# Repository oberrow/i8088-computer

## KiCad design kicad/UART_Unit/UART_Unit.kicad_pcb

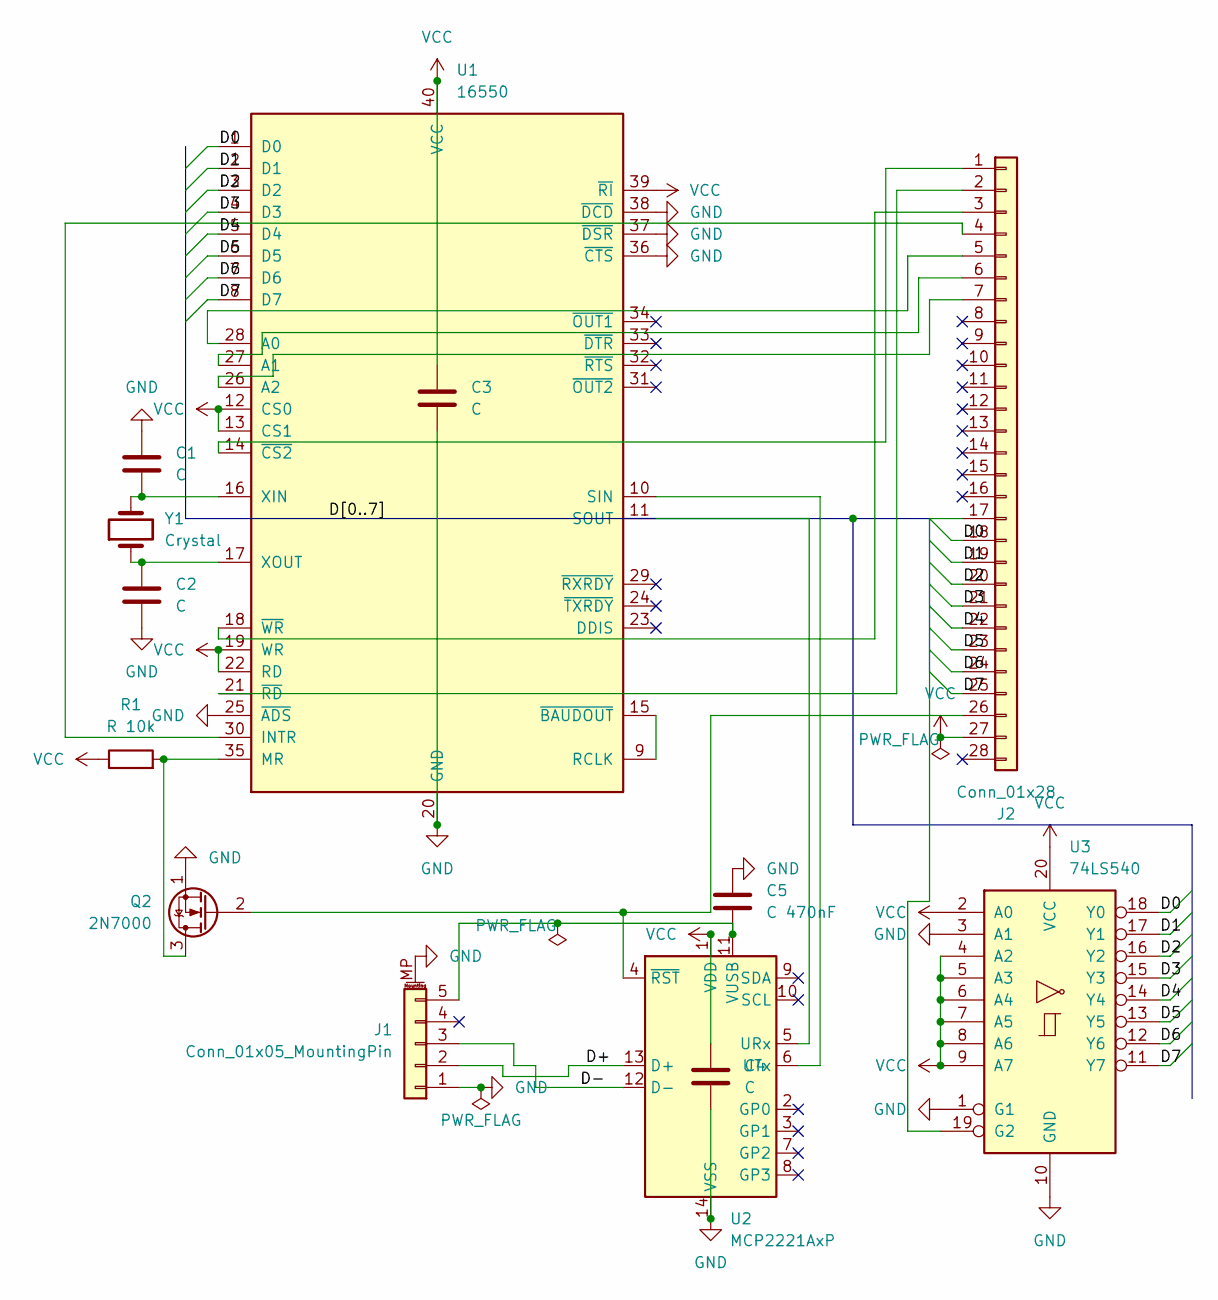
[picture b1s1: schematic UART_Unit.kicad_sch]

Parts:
C1, C2: C; C_Disc_D5.0mm_W2.5mm_P5.00mm
C3, C4: C; C_Disc_D5.0mm_W2.5mm_P2.50mm
C5: C 470nF; C_Disc_D5.0mm_W2.5mm_P2.50mm
J1: Conn_01x05_MountingPin; Molex_200528-0050_1x05-1MP_P1.00mm_Horizontal
J2: Conn_01x28; PinHeader_2x14_P2.54mm_Vertical
Q2: 2N7000; TO-92_Inline
R1: R 10k; R_Axial_DIN0207_L6.3mm_D2.5mm_P10.16mm_Horizontal
U1: 16550; DIP-40_W15.24mm
U2: MCP2221AxP; DIP-14_W7.62mm
U3: 74LS540; DIP-20_W7.62mm
Y1: Crystal; Crystal_HC49-U_Vertical

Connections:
/D0: J2.18, U1.1 (D0), U3.18 (Y0)
/D1: J2.19, U1.2 (D1), U3.17 (Y1)
/D2: J2.20, U1.3 (D2), U3.16 (Y2)
/D3: J2.21, U1.4 (D3), U3.15 (Y3)
/D4: J2.22, U1.5 (D4), U3.14 (Y4)
/D5: J2.23, U1.6 (D5), U3.13 (Y5)
/D6: J2.24, U1.7 (D6), U3.12 (Y6)
/D7: J2.25, U1.8 (D7), U3.11 (Y7)
/D+: J1.2, U2.13 (D+)
/D-: J1.3, U2.12 (D-)
GND: C1.1, C2.2, C3.2, C4.2, C5.1, J1.1, J1.MP (MountPin), Q2.1 (S), U1.20 (GND), U1.25 (~ADS), U1.36 (~CTS), U1.37 (~DSR), U1.38 (~DCD), U2.14 (VSS), U3.1 (G1), U3.3 (A1), U3.10 (GND)
unnamed: C5.2, J1.5, U2.11 (VUSB)
unnamed: J2.1, U1.14 (~CS2)
unnamed: J2.2, U1.21 (~RD)
unnamed: J2.3, U1.18 (~WR)
unnamed: J2.4, U1.30 (INTR)
unnamed: J2.5, U1.28 (A0)
unnamed: J2.6, U1.27 (A1)
unnamed: J2.7, U1.26 (A2)
unnamed: J2.17, U3.19 (G2)
unnamed: J2.26, Q2.2 (G), U2.4 (~RST)
unnamed: Q2.3 (D), R1.2, U1.35 (MR)
unnamed: U1.9 (RCLK), U1.15 (~BAUDOUT)
unnamed: U1.10 (SIN), U2.6 (UTx)
unnamed: U1.11 (SOUT), U2.5 (URx)
unnamed: C1.2, U1.16 (XIN), Y1.2
unnamed: C2.1, U1.17 (XOUT), Y1.1
VCC: C3.1, C4.1, J2.27, R1.1, U1.12 (CS0), U1.13 (CS1), U1.19 (WR), U1.22 (RD), U1.39 (~RI), U1.40 (VCC), U2.1 (VDD), U3.2 (A0), U3.4 (A2), U3.5 (A3), U3.6 (A4), U3.7 (A5), U3.8 (A6), U3.9 (A7), U3.20 (VCC)

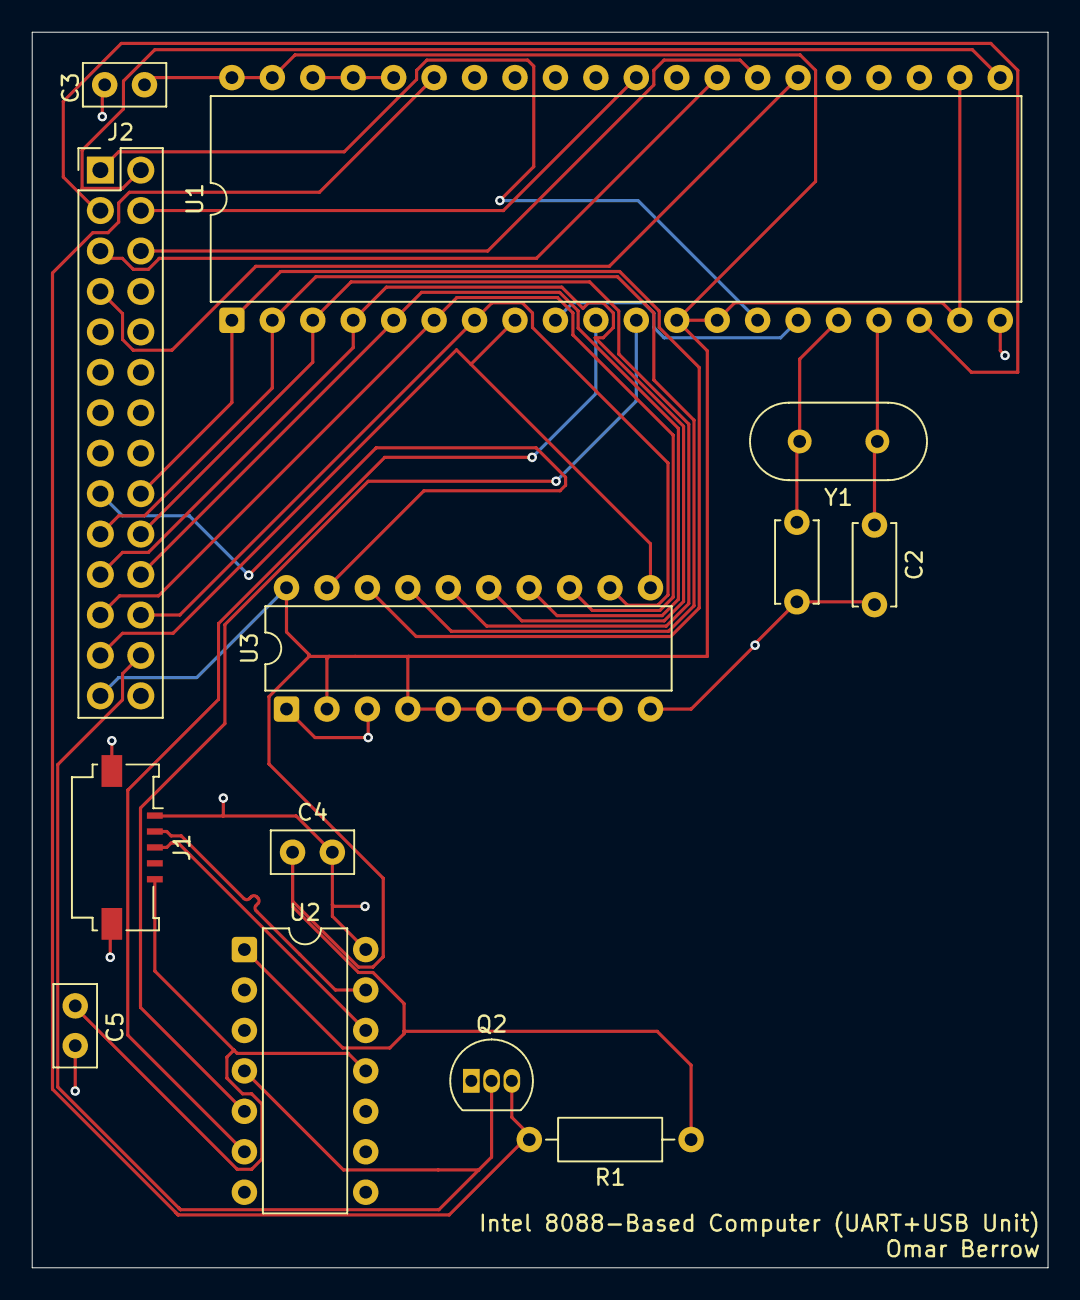
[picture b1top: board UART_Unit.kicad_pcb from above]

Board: 2 copper layers, 63.8 x 77.6 mm, 13 parts (0 on the bottom side), 28 nets.

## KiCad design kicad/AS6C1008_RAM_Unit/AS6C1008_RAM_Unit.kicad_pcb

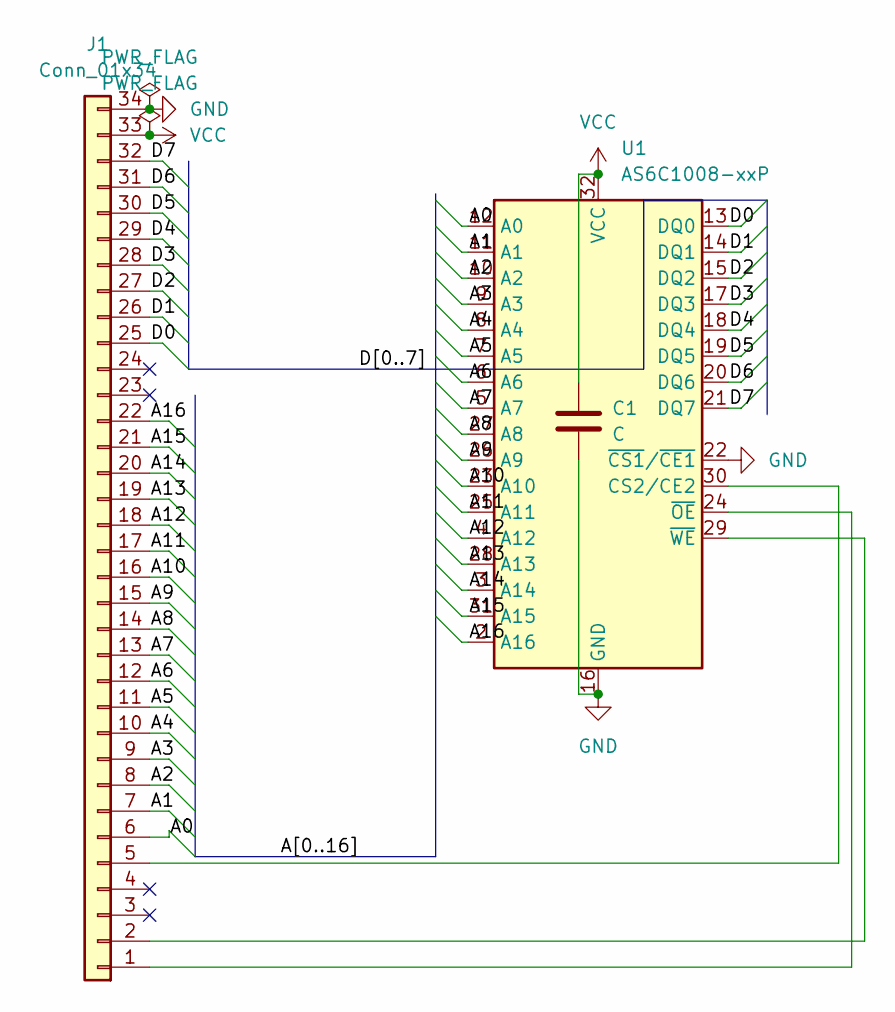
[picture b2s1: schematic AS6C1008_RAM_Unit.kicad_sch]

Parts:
C1: C; C_Disc_D5.0mm_W2.5mm_P2.50mm
J1: Conn_01x34; PinHeader_2x17_P2.54mm_Vertical
U1: AS6C1008-xxP; DIP-32_W15.24mm

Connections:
/A0: J1.6, U1.12 (A0)
/A1: J1.7, U1.11 (A1)
/A2: J1.8, U1.10 (A2)
/A3: J1.9, U1.9 (A3)
/A4: J1.10, U1.8 (A4)
/A5: J1.11, U1.7 (A5)
/A6: J1.12, U1.6 (A6)
/A7: J1.13, U1.5 (A7)
/A8: J1.14, U1.27 (A8)
/A9: J1.15, U1.26 (A9)
/A10: J1.16, U1.23 (A10)
/A11: J1.17, U1.25 (A11)
/A12: J1.18, U1.4 (A12)
/A13: J1.19, U1.28 (A13)
/A14: J1.20, U1.3 (A14)
/A15: J1.21, U1.31 (A15)
/A16: J1.22, U1.2 (A16)
/D0: J1.25, U1.13 (DQ0)
/D1: J1.26, U1.14 (DQ1)
/D2: J1.27, U1.15 (DQ2)
/D3: J1.28, U1.17 (DQ3)
/D4: J1.29, U1.18 (DQ4)
/D5: J1.30, U1.19 (DQ5)
/D6: J1.31, U1.20 (DQ6)
/D7: J1.32, U1.21 (DQ7)
GND: C1.2, J1.34, U1.16 (GND), U1.22 (~CS1/~CE1)
unnamed: J1.1, U1.24 (~OE)
unnamed: J1.2, U1.29 (~WE)
unnamed: J1.5, U1.30 (CS2/CE2)
VCC: C1.1, J1.33, U1.32 (VCC)

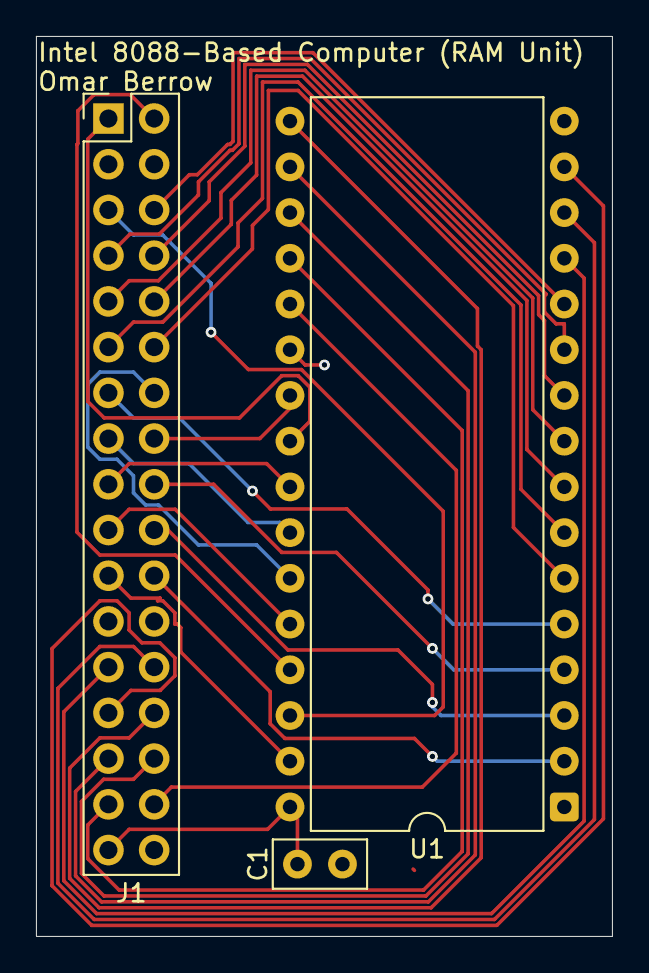
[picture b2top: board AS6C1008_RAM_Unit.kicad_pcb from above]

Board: 2 copper layers, 32.0 x 50.0 mm, 3 parts (0 on the bottom side), 30 nets.

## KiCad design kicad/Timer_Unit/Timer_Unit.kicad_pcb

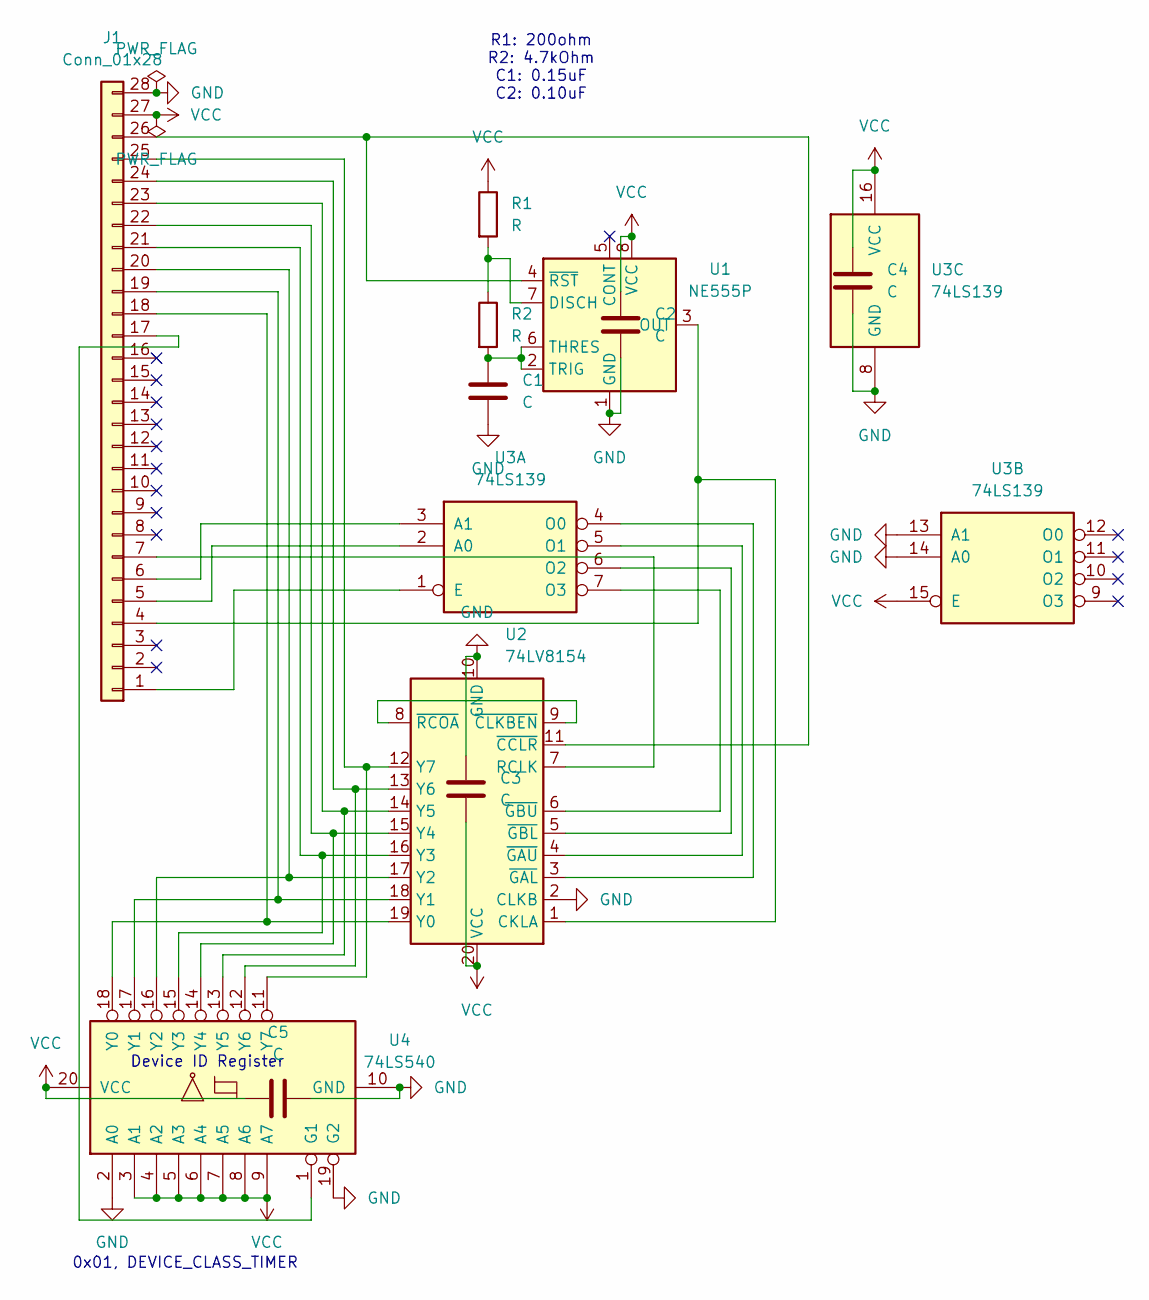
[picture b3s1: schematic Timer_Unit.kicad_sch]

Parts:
C1, C2, C3, C4, C5: C; C_Disc_D5.0mm_W2.5mm_P2.50mm
J1: Conn_01x28; PinHeader_2x14_P2.54mm_Vertical
R1, R2: R; R_Axial_DIN0207_L6.3mm_D2.5mm_P10.16mm_Horizontal
U1: NE555P; DIP-8_W7.62mm
U2: 74LV8154; DIP-20_W7.62mm
U3: 74LS139; DIP-16_W7.62mm
U4: 74LS540; DIP-20_W7.62mm

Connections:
GND: C1.2, C2.2, C3.1, C4.2, C5.2, J1.28, U1.1 (GND), U2.2 (CLKB), U2.10 (GND), U3.8 (GND), U3.13 (A1), U3.14 (A0), U4.2 (A0), U4.10 (GND), U4.19 (G2)
unnamed: J1.1, U3.1 (E)
unnamed: J1.4, U1.3 (OUT), U2.1 (CKLA)
unnamed: J1.5, U3.2 (A0)
unnamed: J1.6, U3.3 (A1)
unnamed: J1.7, U2.7 (RCLK)
unnamed: J1.17, U4.1 (G1)
unnamed: J1.18, U2.19 (Y0), U4.18 (Y0)
unnamed: J1.19, U2.18 (Y1), U4.17 (Y1)
unnamed: J1.20, U2.17 (Y2), U4.16 (Y2)
unnamed: J1.21, U2.16 (Y3), U4.15 (Y3)
unnamed: J1.22, U2.15 (Y4), U4.14 (Y4)
unnamed: J1.23, U2.14 (Y5), U4.13 (Y5)
unnamed: J1.24, U2.13 (Y6), U4.12 (Y6)
unnamed: J1.25, U2.12 (Y7), U4.11 (Y7)
unnamed: J1.26, U1.4 (~RST), U2.11 (~CCLR)
unnamed: R1.2, R2.1, U1.7 (DISCH)
unnamed: C1.1, R2.2, U1.2 (TRIG), U1.6 (THRES)
unnamed: U2.8 (~RCOA), U2.9 (~CLKBEN)
unnamed: U2.3 (~GAL), U3.4 (O0)
unnamed: U2.4 (~GAU), U3.5 (O1)
unnamed: U2.5 (~GBL), U3.6 (O2)
unnamed: U2.6 (~GBU), U3.7 (O3)
VCC: C2.1, C3.2, C4.1, C5.1, J1.27, R1.1, U1.8 (VCC), U2.20 (VCC), U3.15 (E), U3.16 (VCC), U4.3 (A1), U4.4 (A2), U4.5 (A3), U4.6 (A4), U4.7 (A5), U4.8 (A6), U4.9 (A7), U4.20 (VCC)

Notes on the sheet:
R1: 200ohm R2: 4.7kOhm C1: 0.15uF C2: 0.10uF
Device ID Register
0x01, DEVICE_CLASS_TIMER

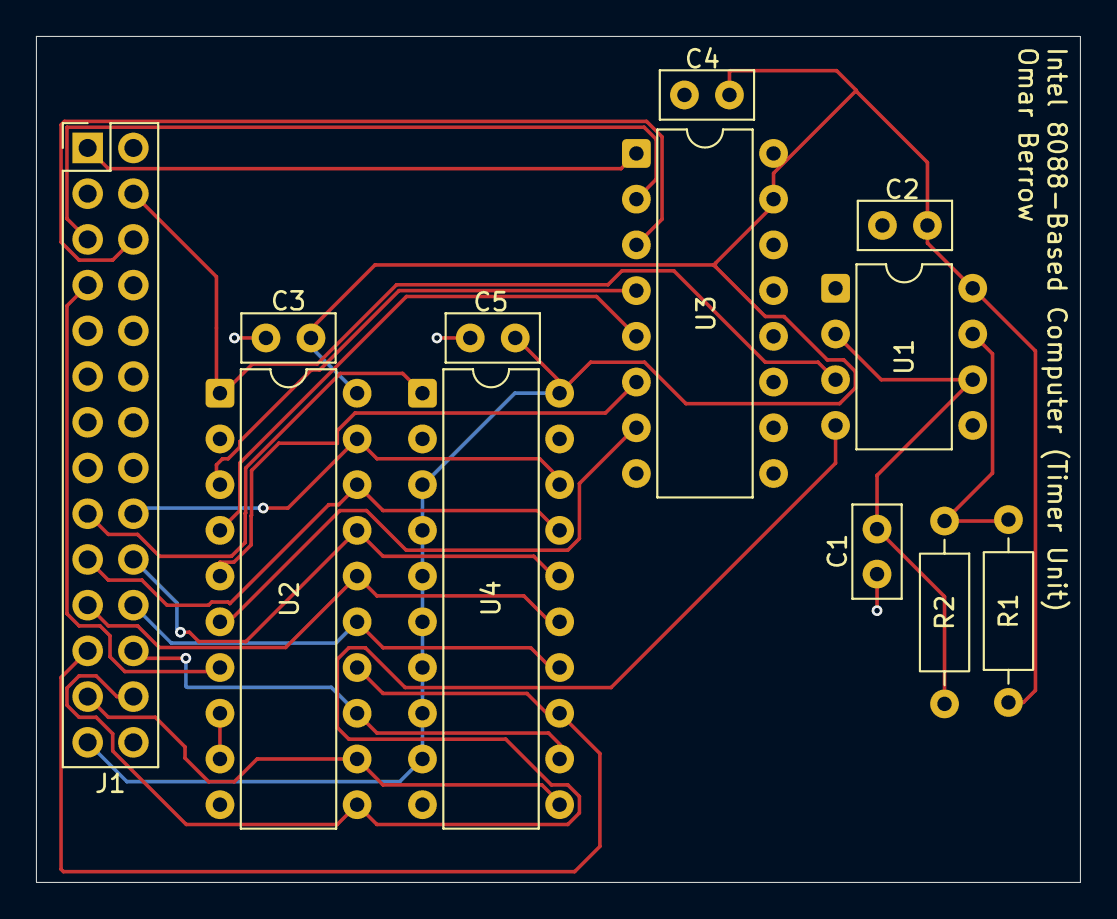
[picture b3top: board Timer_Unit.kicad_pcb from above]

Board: 2 copper layers, 58.0 x 47.0 mm, 12 parts (0 on the bottom side), 24 nets.

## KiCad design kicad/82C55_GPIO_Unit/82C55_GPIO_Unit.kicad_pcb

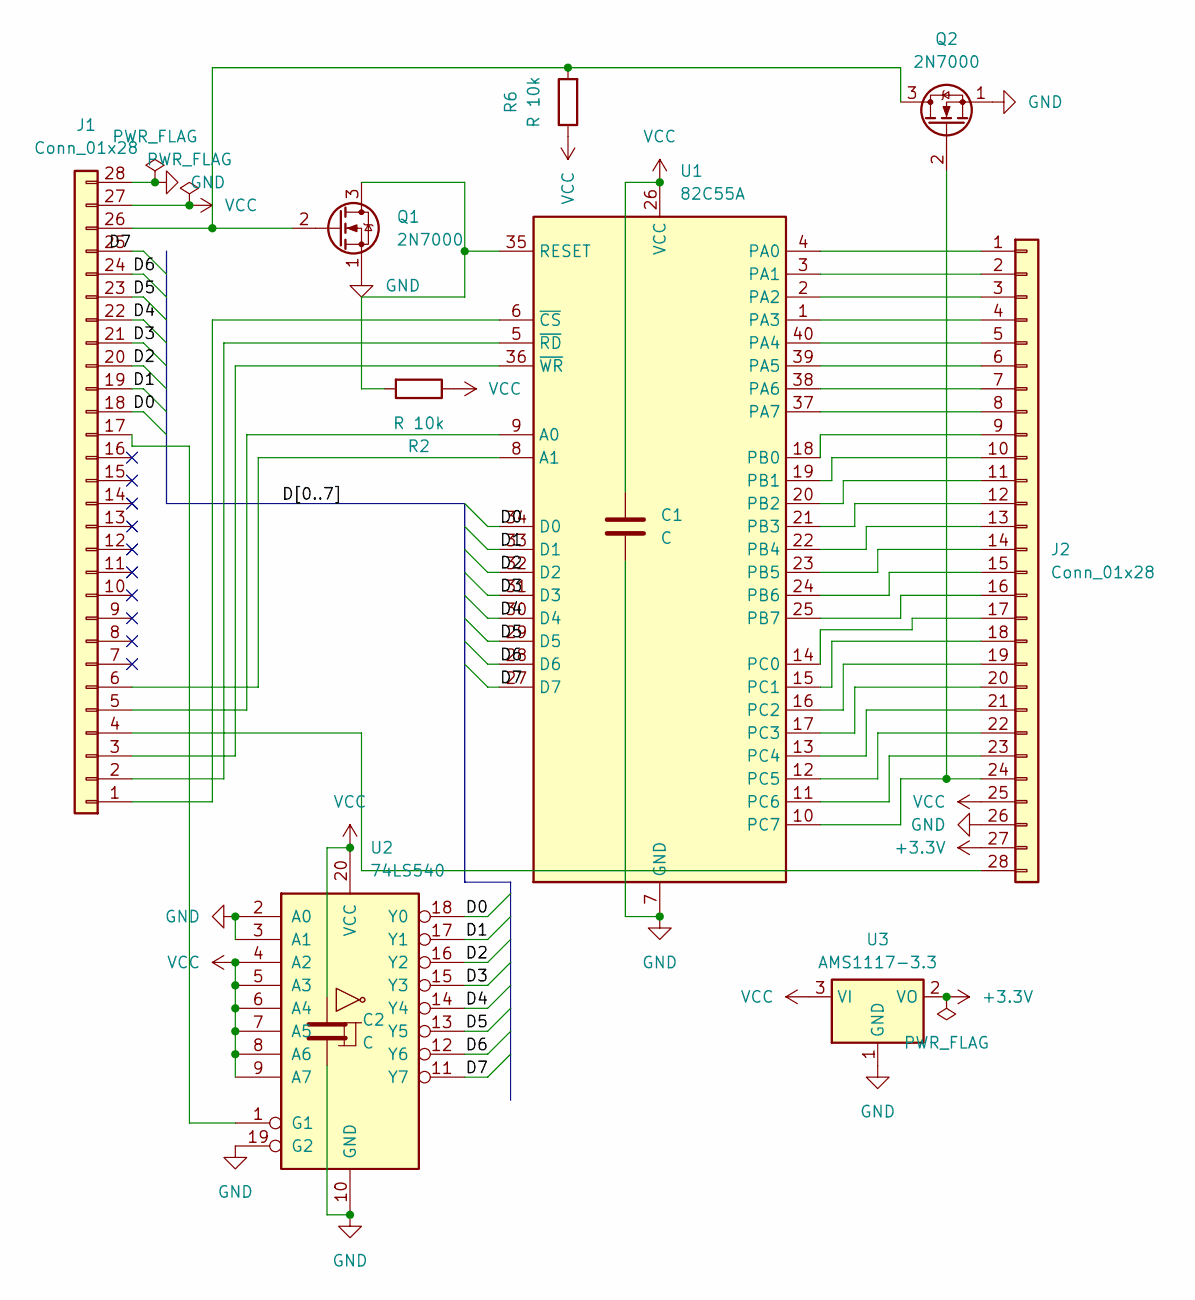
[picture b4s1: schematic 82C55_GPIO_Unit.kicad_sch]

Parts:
C1, C2: C; C_Disc_D5.0mm_W2.5mm_P2.50mm
J1, J2: Conn_01x28; PinHeader_2x14_P2.54mm_Vertical
Q1, Q2: 2N7000; TO-92_Inline
R2, R6: R 10k; R_Axial_DIN0207_L6.3mm_D2.5mm_P10.16mm_Horizontal
U1: 82C55A; DIP-40_W15.24mm
U2: 74LS540; DIP-20_W7.62mm
U3: AMS1117-3.3; SOT-223-3_TabPin2

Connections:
+3.3V: J2.27, U3.2 (VO)
/D0: J1.18, U1.34 (D0), U2.18 (Y0)
/D1: J1.19, U1.33 (D1), U2.17 (Y1)
/D2: J1.20, U1.32 (D2), U2.16 (Y2)
/D3: J1.21, U1.31 (D3), U2.15 (Y3)
/D4: J1.22, U1.30 (D4), U2.14 (Y4)
/D5: J1.23, U1.29 (D5), U2.13 (Y5)
/D6: J1.24, U1.28 (D6), U2.12 (Y6)
/D7: J1.25, U1.27 (D7), U2.11 (Y7)
GND: C1.2, C2.2, J1.28, J2.26, Q1.1 (S), Q2.1 (S), U1.7 (GND), U2.2 (A0), U2.3 (A1), U2.10 (GND), U2.19 (G2), U3.1 (GND)
unnamed: J1.1, U1.6 (~CS)
unnamed: J1.2, U1.5 (~RD)
unnamed: J1.3, U1.36 (~WR)
unnamed: J1.4, J2.28
unnamed: J1.5, U1.9 (A0)
unnamed: J1.6, U1.8 (A1)
unnamed: J1.17, U2.1 (G1)
unnamed: J1.26, Q1.2 (G), Q2.3 (D), R6.2
unnamed: J2.1, U1.4 (PA0)
unnamed: J2.2, U1.3 (PA1)
unnamed: J2.3, U1.2 (PA2)
unnamed: J2.4, U1.1 (PA3)
unnamed: J2.5, U1.40 (PA4)
unnamed: J2.6, U1.39 (PA5)
unnamed: J2.7, U1.38 (PA6)
unnamed: J2.8, U1.37 (PA7)
unnamed: J2.9, U1.18 (PB0)
unnamed: J2.10, U1.19 (PB1)
unnamed: J2.11, U1.20 (PB2)
unnamed: J2.12, U1.21 (PB3)
unnamed: J2.13, U1.22 (PB4)
unnamed: J2.14, U1.23 (PB5)
unnamed: J2.15, U1.24 (PB6)
unnamed: J2.16, U1.25 (PB7)
unnamed: J2.17, U1.14 (PC0)
unnamed: J2.18, U1.15 (PC1)
unnamed: J2.19, U1.16 (PC2)
unnamed: J2.20, U1.17 (PC3)
unnamed: J2.21, U1.13 (PC4)
unnamed: J2.22, U1.12 (PC5)
unnamed: J2.23, U1.11 (PC6)
unnamed: J2.24, Q2.2 (G), U1.10 (PC7)
unnamed: Q1.3 (D), R2.2, U1.35 (RESET)
VCC: C1.1, C2.1, J1.27, J2.25, R2.1, R6.1, U1.26 (VCC), U2.4 (A2), U2.5 (A3), U2.6 (A4), U2.7 (A5), U2.8 (A6), U2.9 (A7), U2.20 (VCC), U3.3 (VI)

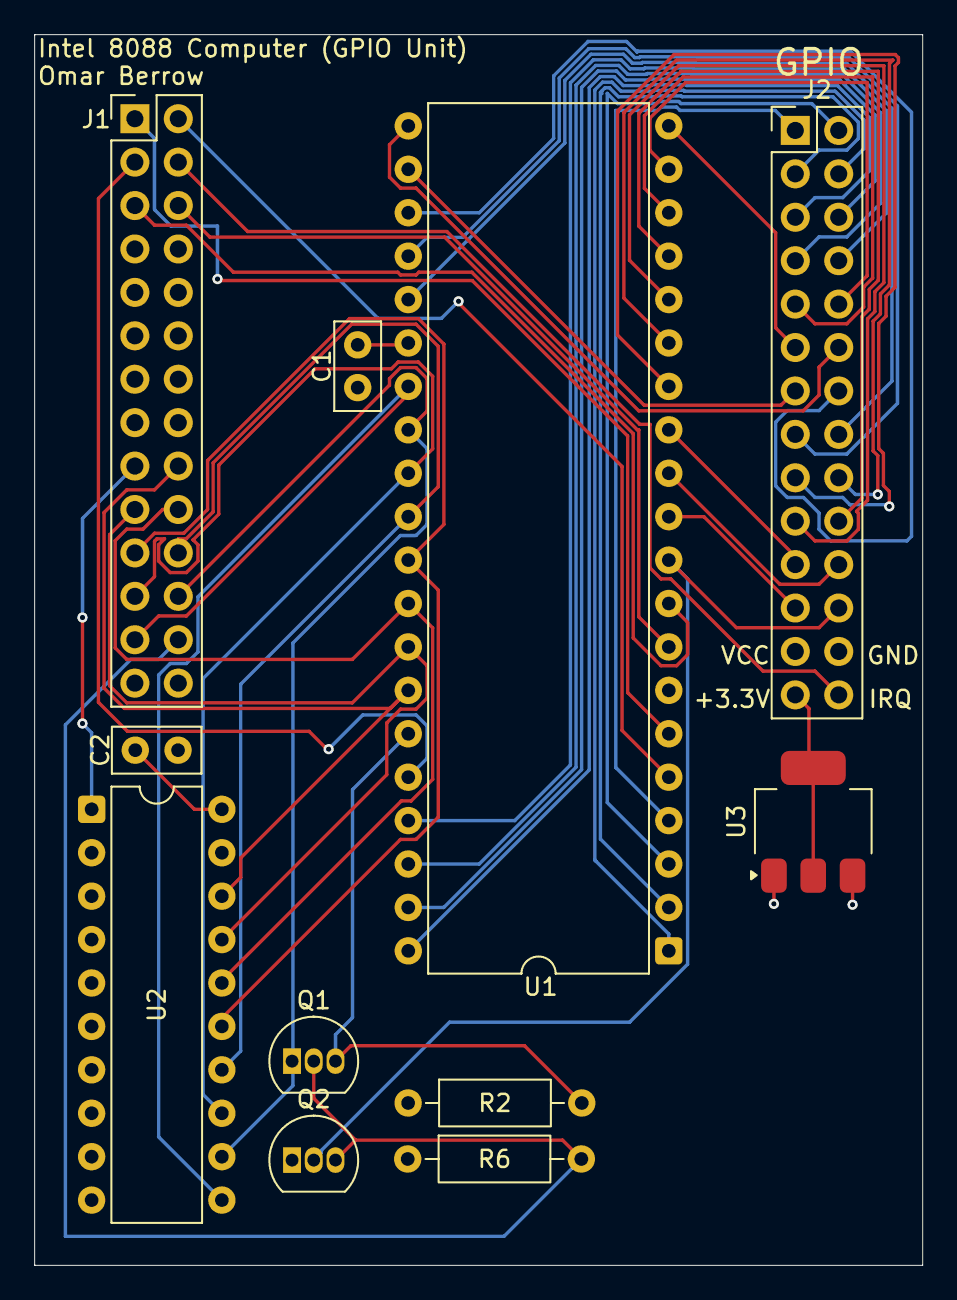
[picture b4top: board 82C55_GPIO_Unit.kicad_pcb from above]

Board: 4 copper layers, 52.0 x 72.0 mm, 11 parts (0 on the bottom side), 44 nets.

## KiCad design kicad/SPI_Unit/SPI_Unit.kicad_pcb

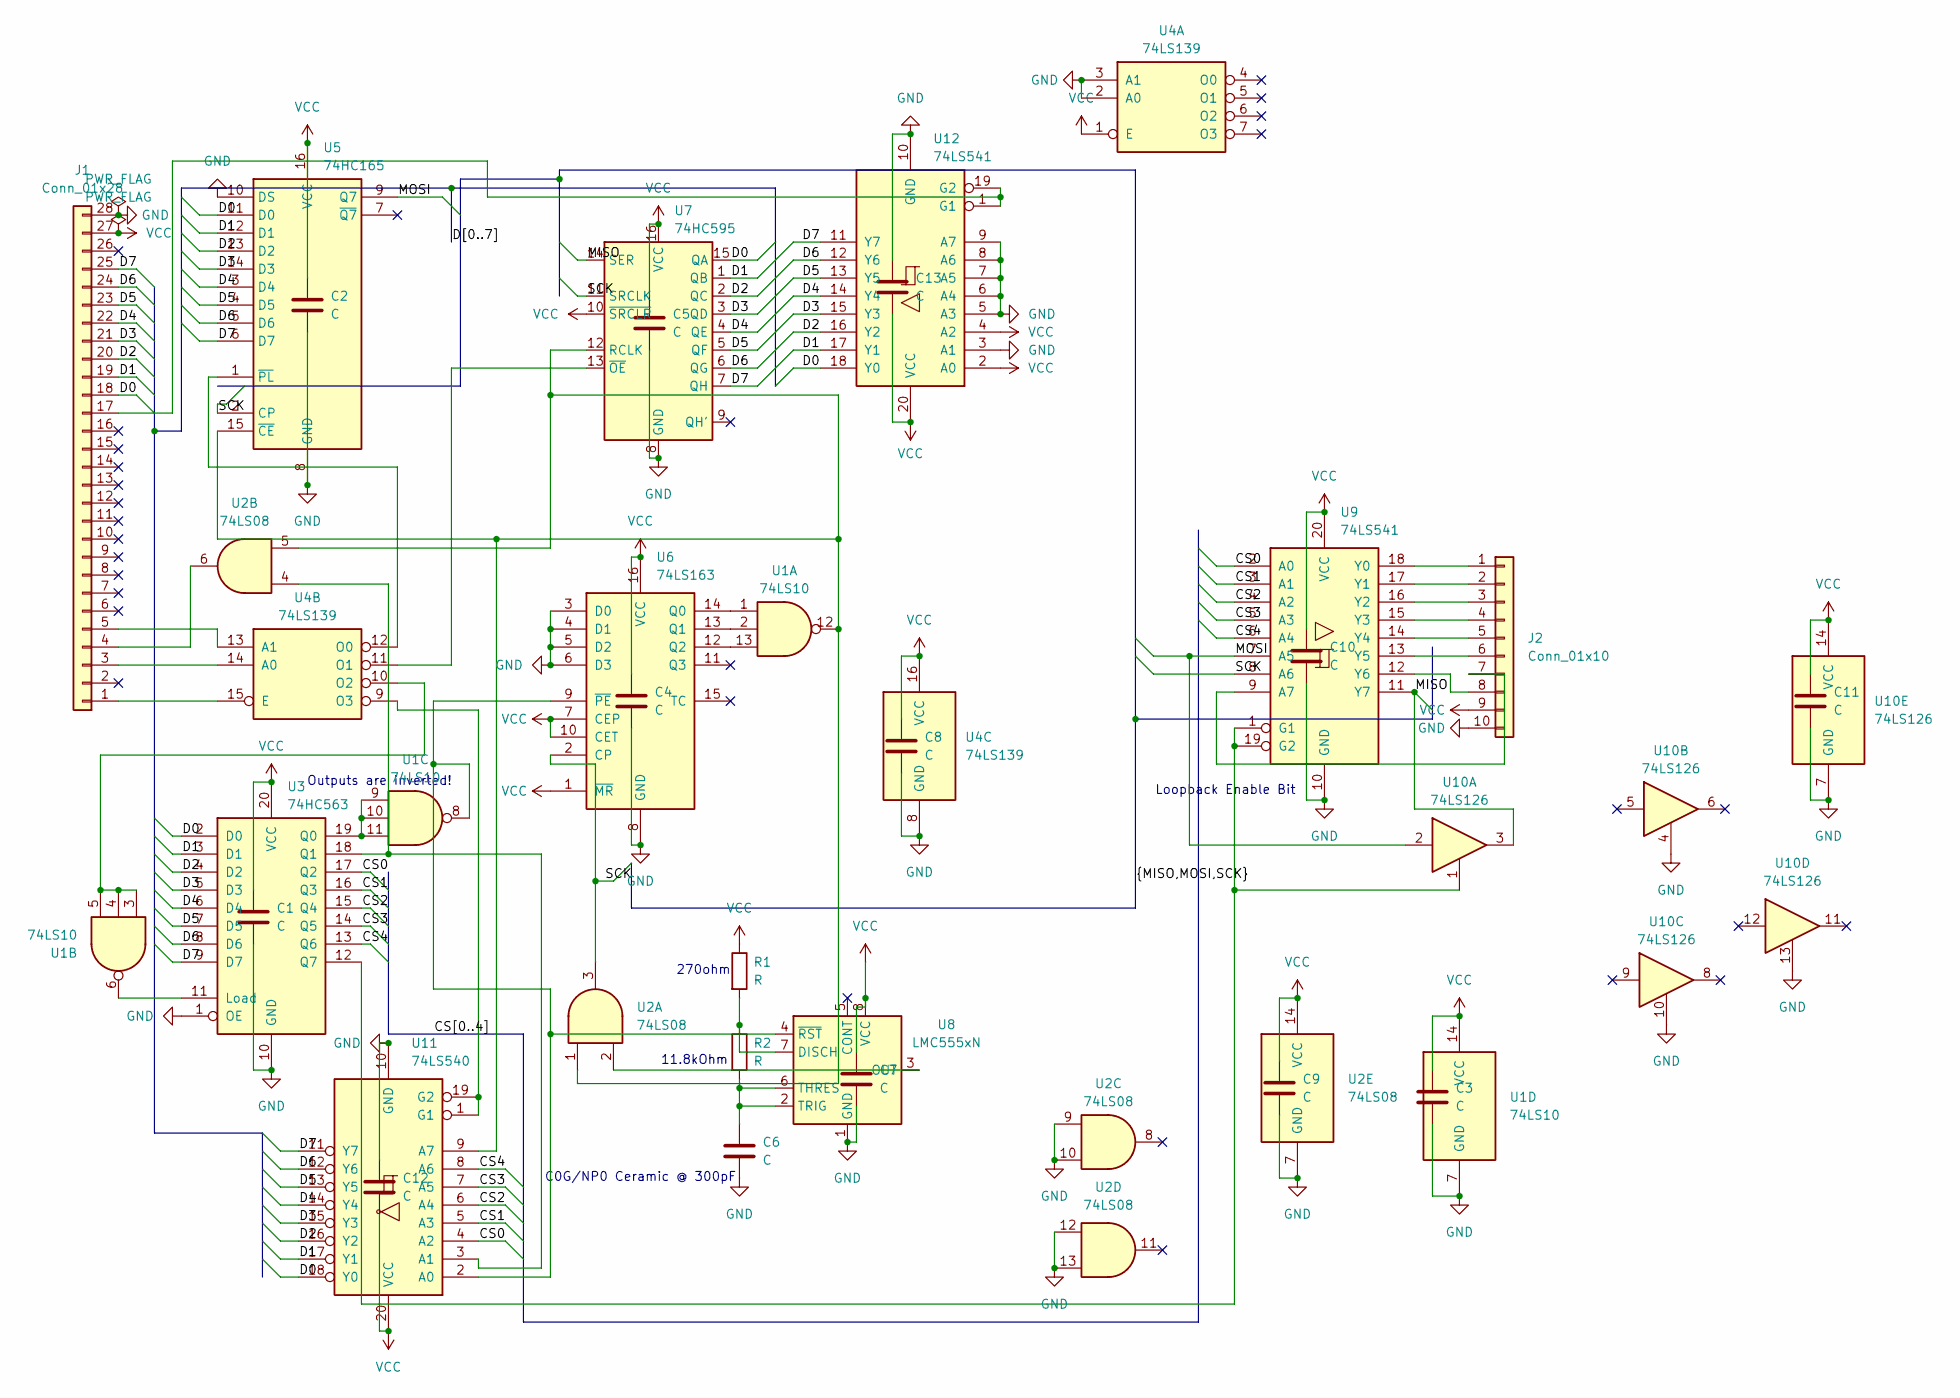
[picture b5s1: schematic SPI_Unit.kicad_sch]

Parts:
C1, C2, C3, C4, C5, C6, C7, C8, C9, C10, C11, C12, C13: C; C_Disc_D5.0mm_W2.5mm_P2.50mm
J1: Conn_01x28; PinHeader_2x14_P2.54mm_Vertical
J2: Conn_01x10; PinHeader_1x10_P2.54mm_Vertical
R1, R2: R; R_Axial_DIN0207_L6.3mm_D2.5mm_P7.62mm_Horizontal
U1: 74LS10; DIP-14_W7.62mm
U2: 74LS08; DIP-14_W7.62mm
U3: 74HC563; DIP-20_W7.62mm
U4: 74LS139; DIP-16_W7.62mm
U5: 74HC165; DIP-16_W7.62mm
U6: 74LS163; DIP-16_W7.62mm
U7: 74HC595; DIP-16_W7.62mm
U8: LMC555xN; DIP-8_W7.62mm
U9, U12: 74LS541; DIP-20_W7.62mm
U10: 74LS126; DIP-14_W7.62mm
U11: 74LS540; DIP-20_W7.62mm

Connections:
/CS0: U3.17 (Q2), U9.2 (A0), U11.4 (A2)
/CS1: U3.16 (Q3), U9.3 (A1), U11.5 (A3)
/CS2: U3.15 (Q4), U9.4 (A2), U11.6 (A4)
/CS3: U3.14 (Q5), U9.5 (A3), U11.7 (A5)
/CS4: U3.13 (Q6), U9.6 (A4), U11.8 (A6)
/D0: J1.18, U3.2 (D0), U5.11 (D0), U7.15 (QA), U11.18 (Y0), U12.18 (Y0)
/D1: J1.19, U3.3 (D1), U5.12 (D1), U7.1 (QB), U11.17 (Y1), U12.17 (Y1)
/D2: J1.20, U3.4 (D2), U5.13 (D2), U7.2 (QC), U11.16 (Y2), U12.16 (Y2)
/D3: J1.21, U3.5 (D3), U5.14 (D3), U7.3 (QD), U11.15 (Y3), U12.15 (Y3)
/D4: J1.22, U3.6 (D4), U5.3 (D4), U7.4 (QE), U11.14 (Y4), U12.14 (Y4)
/D5: J1.23, U3.7 (D5), U5.4 (D5), U7.5 (QF), U11.13 (Y5), U12.13 (Y5)
/D6: J1.24, U3.8 (D6), U5.5 (D6), U7.6 (QG), U11.12 (Y6), U12.12 (Y6)
/D7: J1.25, U3.9 (D7), U5.6 (D7), U7.7 (QH), U11.11 (Y7), U12.11 (Y7)
/MISO: U7.14 (SER), U9.11 (Y7), U10.3
/MOSI: U5.9 (Q7), U9.7 (A5), U10.2
/SCK: U2.3, U5.2 (CP), U6.2 (CP), U7.11 (SRCLK), U9.8 (A6)
GND: C1.2, C2.2, C3.2, C4.2, C5.2, C6.2, C7.2, C8.2, C9.2, C10.2, C11.2, C12.1, C13.1, J1.28, J2.10, U1.7 (GND), U2.7 (GND), U2.9, U2.10, U2.12, U2.13, U3.1 (OE), U3.10 (GND), U4.2 (A0), U4.3 (A1), U4.8 (GND), U5.8 (GND), U5.10 (DS), U6.3 (D0), U6.4 (D1), U6.5 (D2), U6.6 (D3), U6.8 (GND), U7.8 (GND), U8.1 (GND), U9.10 (GND), U10.4, U10.7 (GND), U10.10, U10.13, U11.10 (GND), U12.3 (A1), U12.5 (A3), U12.6 (A4), U12.7 (A5), U12.8 (A6), U12.9 (A7), U12.10 (GND)
unnamed: J1.1, U4.15 (E)
unnamed: J1.3, U4.14 (A0)
unnamed: J1.4, U2.6
unnamed: J1.5, U4.13 (A1)
unnamed: J1.17, U12.1 (G1), U12.19 (G2)
unnamed: J2.1, U9.18 (Y0)
unnamed: J2.2, U9.17 (Y1)
unnamed: J2.3, U9.16 (Y2)
unnamed: J2.4, U9.15 (Y3)
unnamed: J2.5, U9.14 (Y4)
unnamed: J2.6, U9.13 (Y5)
unnamed: J2.7, U9.9 (A7)
unnamed: J2.8, U9.12 (Y6)
unnamed: U1.6, U3.11 (Load)
unnamed: U1.9, U1.10, U1.11, U3.19 (Q0)
unnamed: U3.12 (Q7), U9.1 (G1), U9.19 (G2), U10.1
unnamed: U4.12 (O0), U5.1 (~PL)
unnamed: U4.11 (O1), U7.13 (~OE)
unnamed: U1.3, U1.4, U1.5, U4.10 (O2)
unnamed: U1.1, U6.14 (Q0)
unnamed: U1.2, U6.13 (Q1)
unnamed: U1.13, U6.12 (Q2)
unnamed: R1.2, R2.1, U8.7 (DISCH)
unnamed: U2.2, U8.3 (OUT)
unnamed: C6.1, R2.2, U8.2 (TRIG), U8.6 (THRES)
unnamed: U1.8, U6.9 (~PE), U8.4 (~RST), U11.2 (A0)
unnamed: U2.4, U3.18 (Q1), U11.3 (A1)
unnamed: U1.12, U2.1, U2.5, U5.15 (~CE), U7.12 (RCLK), U11.9 (A7)
unnamed: U4.9 (O3), U11.1 (G1), U11.19 (G2)
VCC: C1.1, C2.1, C3.1, C4.1, C5.1, C7.1, C8.1, C9.1, C10.1, C11.1, C12.2, C13.2, J1.27, J2.9, R1.1, U1.14 (VCC), U2.14 (VCC), U3.20 (VCC), U4.1 (E), U4.16 (VCC), U5.16 (VCC), U6.1 (~MR), U6.7 (CEP), U6.10 (CET), U6.16 (VCC), U7.10 (~SRCLR), U7.16 (VCC), U8.8 (VCC), U9.20 (VCC), U10.14 (VCC), U11.20 (VCC), U12.2 (A0), U12.4 (A2), U12.20 (VCC)

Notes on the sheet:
Loopback Enable Bit
C0G/NP0 Ceramic @ 300pF
270ohm
Outputs are inverted!
11.8kOhm

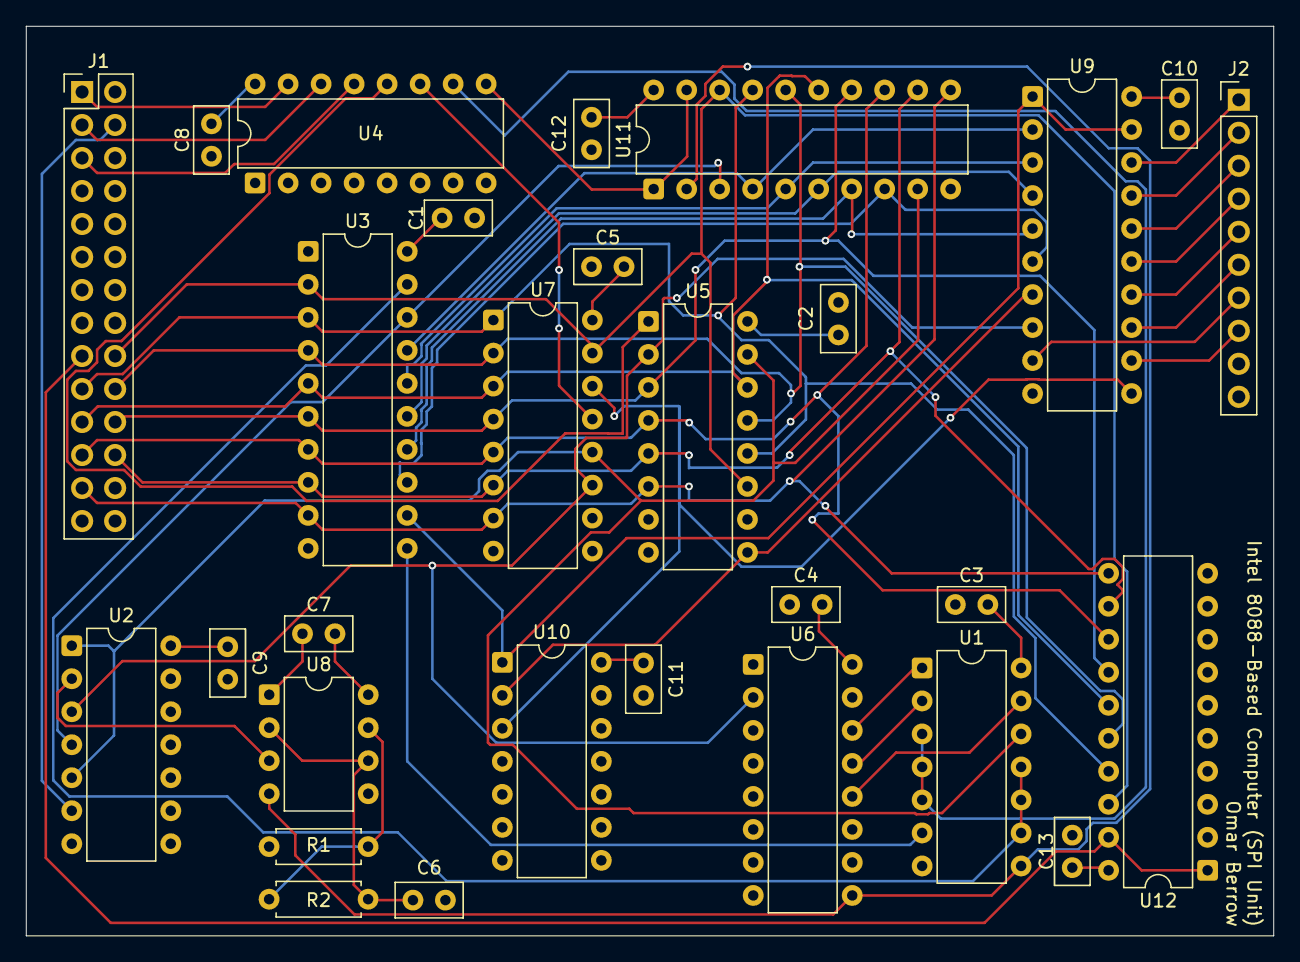
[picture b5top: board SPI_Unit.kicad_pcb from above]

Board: 4 copper layers, 96.0 x 70.0 mm, 29 parts (0 on the bottom side), 47 nets.
